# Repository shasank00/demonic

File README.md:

# Description:
A Cow demon that constantly gazes at you from you keychain and is waiting for it's moment to attack. The demon shows it's true nature in the dark when it's third eye awakens and it starts to shiver violently.
# Parts list:
Battery x1 Push Switch x2 Resistor x5 LED x3 Mini Motor x1 NPN-Transistor x1 Photoresistor x1
# Some glimpses

# Slack id:shresthashasank59

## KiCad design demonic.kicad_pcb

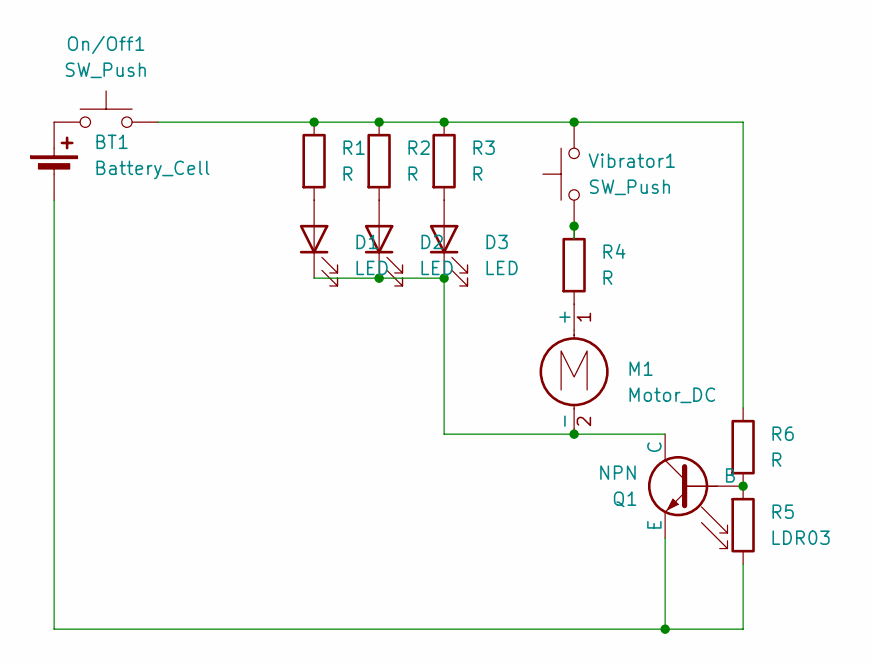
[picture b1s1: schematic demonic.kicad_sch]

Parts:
BT1: Battery_Cell; BatteryHolder_Keystone_3034_1x20mm
D1, D2, D3: LED; LED_D5.0mm
M1: Motor_DC; PinHeader_1x02_P2.54mm_Vertical
On/Off1: SW_Push; SW_PUSH_6mm
Q1: NPN; TO-92L_HandSolder
R1, R2, R3, R4, R6: R; R_Axial_DIN0207_L6.3mm_D2.5mm_P7.62mm_Horizontal
R5: LDR03; R_LDR_5.1x4.3mm_P3.4mm_Vertical
Vibrator1: SW_Push; SW_PUSH_6mm

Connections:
unnamed: BT1.1 (+), On/Off1.1
unnamed: BT1.2 (-), Q1.3 (E), R5.2
unnamed: D1.2 (A), R1.2
unnamed: D1.1 (K), D2.1 (K), D3.1 (K), M1.2 (-), Q1.1 (C)
unnamed: D2.2 (A), R2.2
unnamed: D3.2 (A), R3.2
unnamed: M1.1 (+), R4.2
unnamed: On/Off1.2, R1.1, R2.1, R3.1, R6.1, Vibrator1.2
unnamed: Q1.2 (B), R5.1, R6.2
unnamed: R4.1, Vibrator1.1

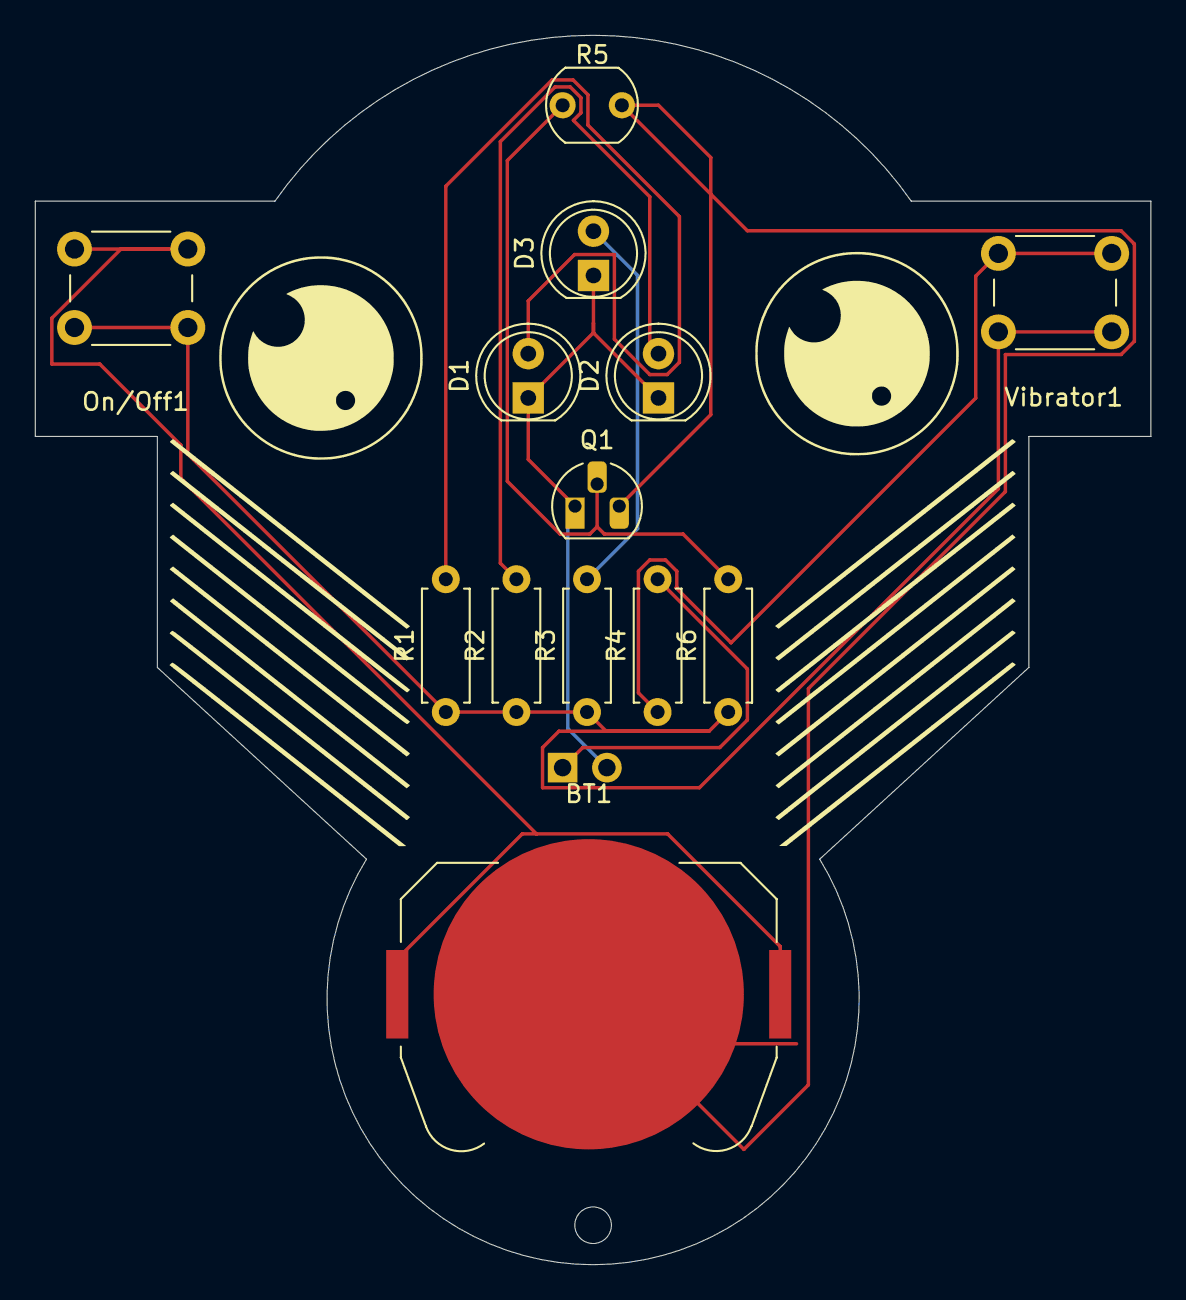
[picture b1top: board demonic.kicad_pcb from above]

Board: 2 copper layers, 64.0 x 70.5 mm, 14 parts (1 on the bottom side), 10 nets.

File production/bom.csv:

Designator,Footprint,Quantity,Value,LCSC Part #
BT1,BatteryHolder_Keystone_3034_1x20mm,1,Battery_Cell,
"D1, D2, D3",LED_D5.0mm,3,LED,
M1,PinHeader_1x02_P2.54mm_Vertical,1,Motor_DC,
"ON/OFF1, VIBRATOR1",SW_PUSH_6mm,2,SW_Push,
Q1,TO-92L_HandSolder,1,NPN,
"R1, R2, R3, R4, R6",R_Axial_DIN0207_L6.3mm_D2.5mm_P7.62mm_Horizontal,5,R,
R5,R_LDR_5.1x4.3mm_P3.4mm_Vertical,1,LDR03,
